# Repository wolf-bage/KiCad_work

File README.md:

Well this a repo for all my Kicad work to this point, 
that i want to publish and use in my electrical engineering studies

I'm planning to keep all my kicad footprints/symbols and porjects here since it is easy to 
show and import to kicad or a differnet porgram for pcb work

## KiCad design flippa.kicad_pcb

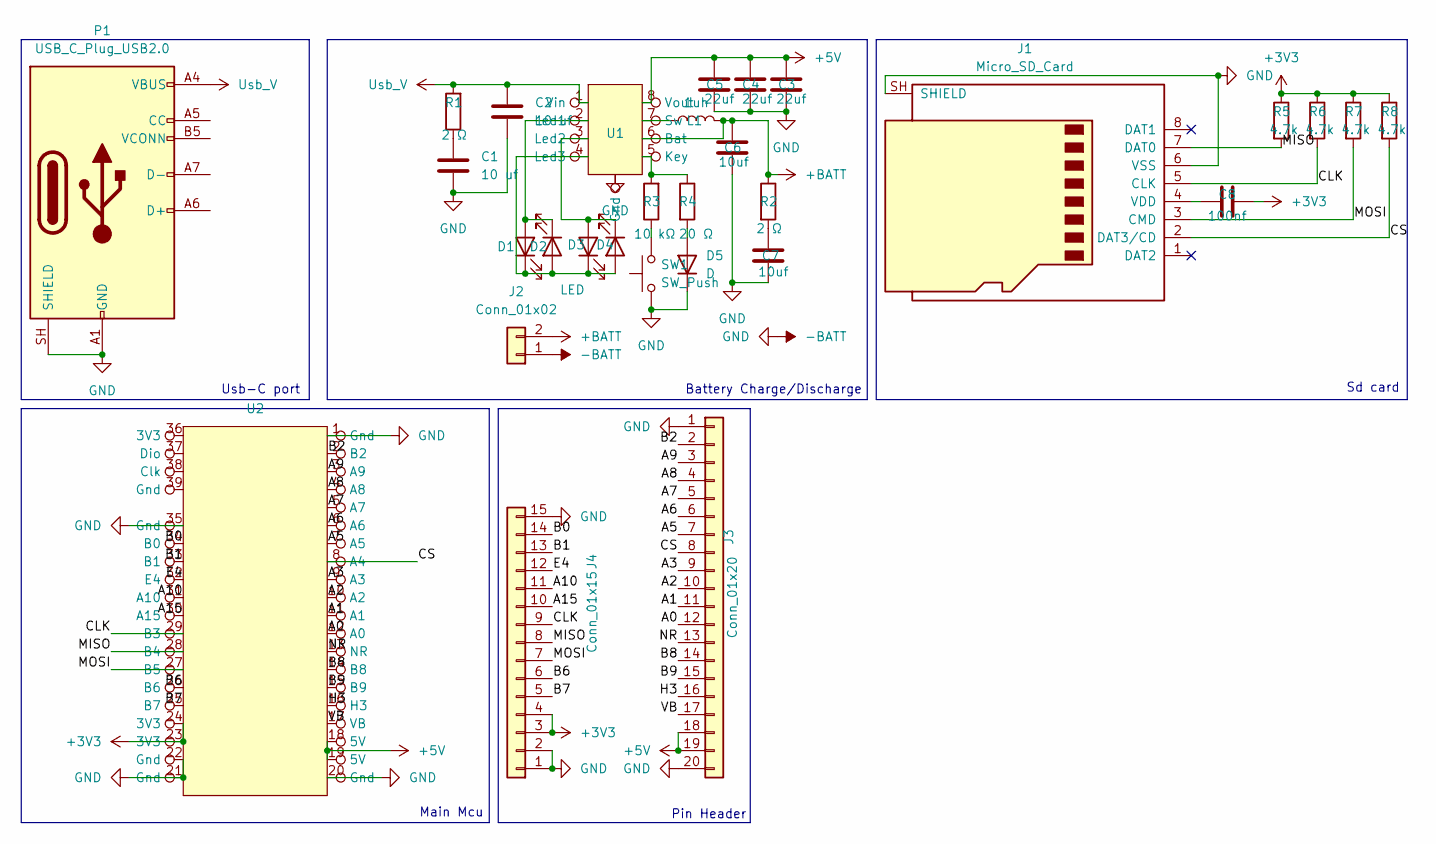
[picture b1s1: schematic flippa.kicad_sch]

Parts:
C1, C2: 10 uf; C_0805_2012Metric
C3, C4, C5: 22uf; C_0805_2012Metric
C6, C7: 10uf; C_0805_2012Metric
C8: 100nf; C_0805_2012Metric
D1, D2, D3, D4: LED; LED_0805_2012Metric
D5: D; D_0805_2012Metric
J1: Micro_SD_Card; microSD_HC_Wuerth_693072010801
J2: Conn_01x02; JST_PH_S2B-PH-K_1x02_P2.00mm_Horizontal
J3: Conn_01x20; PinHeader_1x20_P2.00mm_Vertical
J4: Conn_01x15; PinHeader_1x15_P2.00mm_Vertical
L1: 1uh; L_0805_2012Metric
P1: USB_C_Plug_USB2.0; USB_C_Receptacle_GCT_USB4105-xx-A_16P_TopMnt_Horizontal
R1, R2: 2 Ω; R_0805_2012Metric
R3: 10 kΩ; R_0805_2012Metric
R4: 20 Ω; R_0805_2012Metric
R5, R6, R7, R8: 4.7k; R_0805_2012Metric
SW1: SW_Push; SW_Push_1P1T_NO_CK_KMR2
U1: IP5306
U2: We_Act_STM32_WB55CGU6

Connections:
+3V3: C8.2, J4.3, J4.4, R5.1, R6.1, R7.1, R8.1, U2.23 (3V3), U2.24 (3V3)
+5V: C3.1, C4.1, C5.1, J3.18, J3.19, U1.8 (Vout), U2.18 (5V), U2.19 (5V)
+BATT: C6.1, J2.2, L1.2, R2.1, U1.6 (Bat)
-BATT: C1.2, C2.2, C3.2, C4.2, C5.2, C6.2, C7.1, D5.1 (K), J1.6 (VSS), J1.SH (SHIELD), J2.1, J3.1, J3.20, J4.1, J4.2, J4.15, P1.A1 (GND), P1.A12 (GND), P1.B1 (GND), P1.B12 (GND), P1.SH (SHIELD), SW1.1, U1. (Gnd), U2.1 (Gnd), U2.20 (Gnd), U2.21 (Gnd), U2.22 (Gnd), U2.35 (Gnd)
/A0: J3.12, U2.12 (A0)
/A1: J3.11, U2.11 (A1)
/A2: J3.10, U2.10 (A2)
/A3: J3.9, U2.9 (A3)
/A5: J3.7, U2.7 (A5)
/A6: J3.6, U2.6 (A6)
/A7: J3.5, U2.5 (A7)
/A8: J3.4, U2.4 (A8)
/A9: J3.3, U2.3 (A9)
/A10: J4.11, U2.31 (A10)
/A15: J4.10, U2.30 (A15)
/B0: J4.14, U2.34 (B0)
/B1: J4.13, U2.33 (B1)
/B2: J3.2, U2.2 (B2)
/B6: J4.6, U2.26 (B6)
/B7: J4.5, U2.25 (B7)
/B8: J3.14, U2.14 (B8)
/B9: J3.15, U2.15 (B9)
/CLK: J1.5 (CLK), J4.9, R6.2, U2.29 (B3)
/CS: J1.2 (DAT3/CD), J3.8, R8.2, U2.8 (A4)
/E4: J4.12, U2.32 (E4)
/H3: J3.16, U2.16 (H3)
/MISO: J1.7 (DAT0), J4.8, R5.2, U2.28 (B4)
/MOSI: J1.3 (CMD), J4.7, R7.2, U2.27 (B5)
/NR: J3.13, U2.13 (NR)
/VB: J3.17, U2.17 (VB)
unnamed: C1.1, R1.1
unnamed: C7.2, R2.2
unnamed: D1.2 (A), D2.1 (K), U1.2 (Led1)
unnamed: D1.1 (K), D2.2 (A), D3.1 (K), D4.2 (A), U1.4 (Led3)
unnamed: D3.2 (A), D4.1 (K), U1.3 (Led2)
unnamed: D5.2 (A), R4.2
unnamed: C8.1, J1.4 (VDD)
unnamed: R3.1, SW1.2
unnamed: R3.2, R4.1, U1.5 (Key)
unnamed: L1.1, U1.7 (Sw)
Usb_V: C2.1, P1.A4 (VBUS), P1.A9 (VBUS), P1.B4 (VBUS), P1.B9 (VBUS), R1.2, U1.1 (Vin)

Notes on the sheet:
Main Mcu
Usb-C port
Battery Charge/Discharge
Pin Header
Sd card

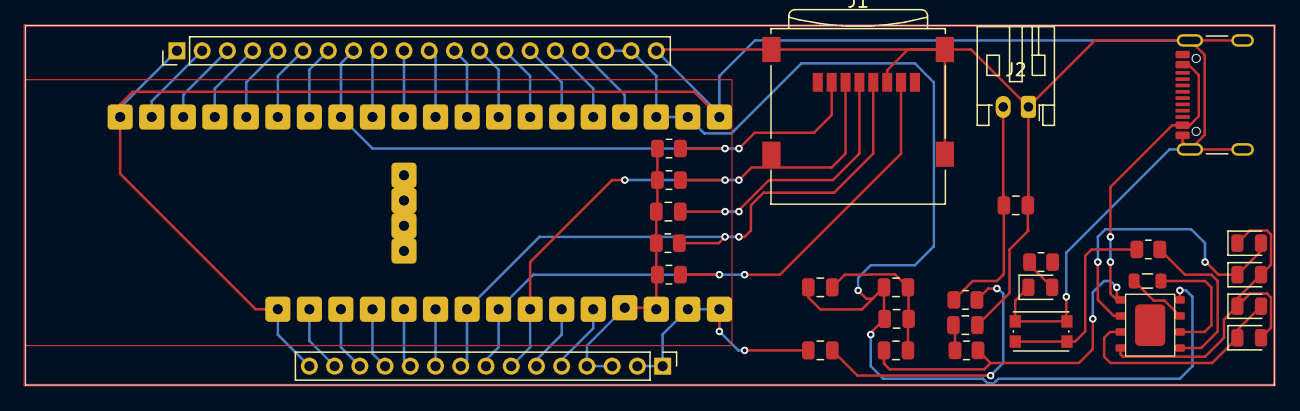
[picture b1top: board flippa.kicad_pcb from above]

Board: 2 copper layers, 99.0 x 28.5 mm, 30 parts (0 on the bottom side), 41 nets.
